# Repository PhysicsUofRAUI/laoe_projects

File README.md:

# laoe_projects
A place to hold all projects I have made while reading the book Learning The Art of Electronics

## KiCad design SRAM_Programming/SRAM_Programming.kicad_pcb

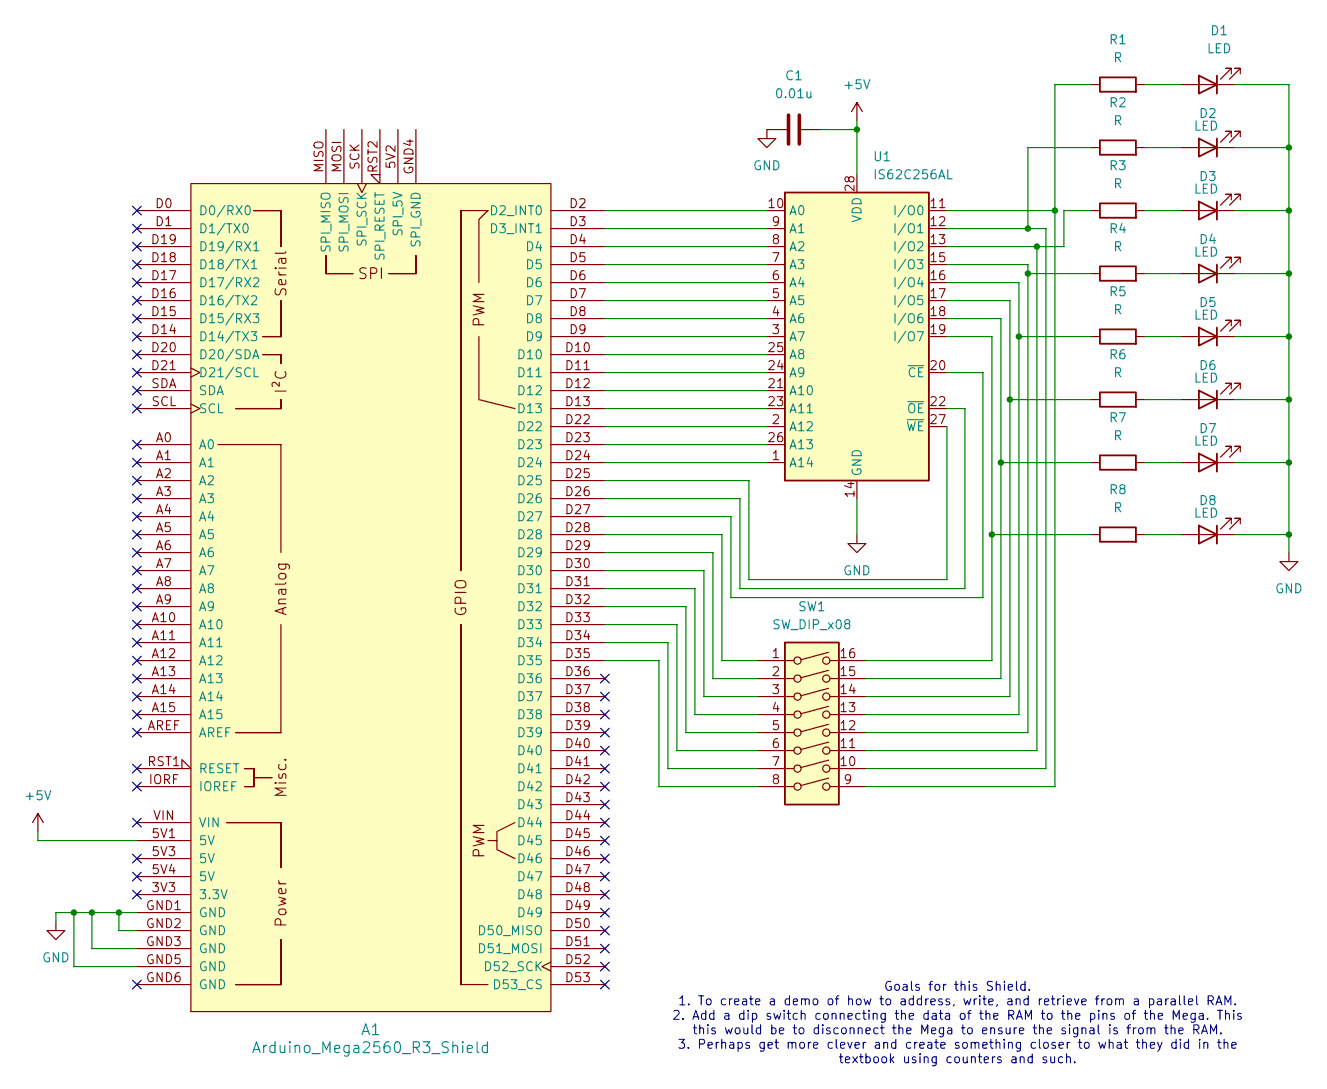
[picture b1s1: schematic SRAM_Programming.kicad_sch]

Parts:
A1: Arduino_Mega2560_R3_Shield
C1: 0.01u; C_0805_2012Metric_Pad1.18x1.45mm_HandSolder; MfG # C0805C103K5RACTU
D1, D2, D3, D4, D5, D6, D7, D8: LED; LED_D5.0mm; MfG # HLMP-D150
R1, R2, R3, R4, R5, R6, R7, R8: R; R_Axial_DIN0309_L9.0mm_D3.2mm_P12.70mm_Horizontal; MfG # CF14JT3K30
SW1: SW_DIP_x08; SW_DIP_SPSTx08_Slide_6.7x21.88mm_W7.62mm_P2.54mm_LowProfile; MfG # 208-8
U1: IS62C256AL; SOP-28_8.4x18.16mm_P1.27mm

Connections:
+5V: A1.5V1 (5V), C1.1, U1.28 (VDD)
GND: A1.GND1 (GND), A1.GND2 (GND), A1.GND3 (GND), A1.GND5 (GND), C1.2, D1.1 (K), D2.1 (K), D3.1 (K), D4.1 (K), D5.1 (K), D6.1 (K), D7.1 (K), D8.1 (K), U1.14 (GND)
unnamed: A1.D2 (D2_INT0), U1.10 (A0)
unnamed: A1.D3 (D3_INT1), U1.9 (A1)
unnamed: A1.D28, SW1.1
unnamed: A1.D29, SW1.2
unnamed: A1.D30, SW1.3
unnamed: A1.D31, SW1.4
unnamed: A1.D32, SW1.5
unnamed: A1.D33, SW1.6
unnamed: A1.D34, SW1.7
unnamed: A1.D35, SW1.8
unnamed: D1.2 (A), R1.2
unnamed: D2.2 (A), R2.2
unnamed: D3.2 (A), R3.2
unnamed: D4.2 (A), R4.2
unnamed: D5.2 (A), R5.2
unnamed: D6.2 (A), R6.2
unnamed: D7.2 (A), R7.2
unnamed: D8.2 (A), R8.2
unnamed: A1.D4, U1.8 (A2)
unnamed: A1.D5, U1.7 (A3)
unnamed: A1.D6, U1.6 (A4)
unnamed: A1.D7, U1.5 (A5)
unnamed: A1.D8, U1.4 (A6)
unnamed: A1.D9, U1.3 (A7)
unnamed: A1.D10, U1.25 (A8)
unnamed: A1.D11, U1.24 (A9)
unnamed: A1.D12, U1.21 (A10)
unnamed: A1.D13, U1.23 (A11)
unnamed: A1.D22, U1.2 (A12)
unnamed: A1.D23, U1.26 (A13)
unnamed: A1.D24, U1.1 (A14)
unnamed: R1.1, SW1.9, U1.11 (I/O0)
unnamed: R2.1, SW1.10, U1.12 (I/O1)
unnamed: R3.1, SW1.11, U1.13 (I/O2)
unnamed: R4.1, SW1.12, U1.15 (I/O3)
unnamed: R5.1, SW1.13, U1.16 (I/O4)
unnamed: R6.1, SW1.14, U1.17 (I/O5)
unnamed: R7.1, SW1.15, U1.18 (I/O6)
unnamed: R8.1, SW1.16, U1.19 (I/O7)
unnamed: A1.D27, U1.20 (~CE)
unnamed: A1.D26, U1.22 (~OE)
unnamed: A1.D25, U1.27 (~WE)

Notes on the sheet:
Goals for this Shield. 1. To create a demo of how to address, write, and retrieve from a parallel RAM. 2. Add a dip switch connecting the data of the RAM to the pins of the Mega. This this would be to disconnect the Mega to ensure the signal is from the RAM. 3. Perhaps get more clever and create so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

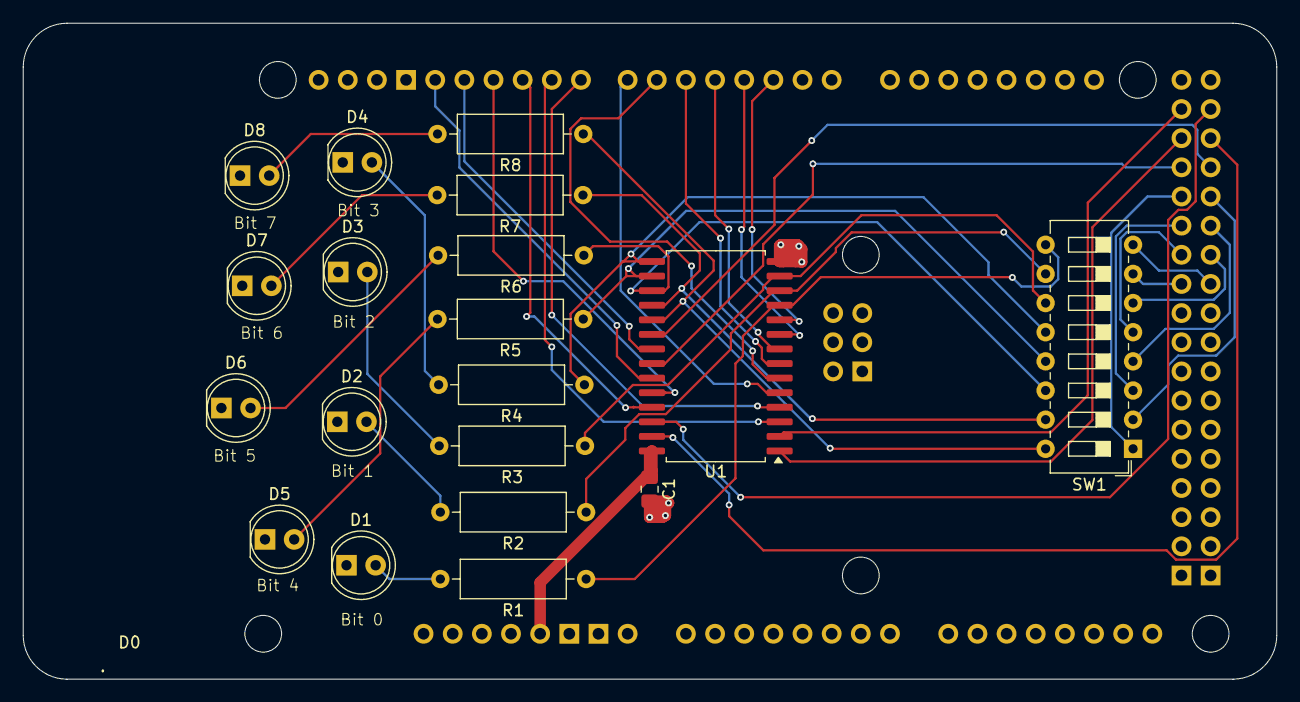
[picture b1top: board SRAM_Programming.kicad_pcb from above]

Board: 2 copper layers, 109.2 x 57.1 mm, 20 parts (0 on the bottom side), 44 nets.

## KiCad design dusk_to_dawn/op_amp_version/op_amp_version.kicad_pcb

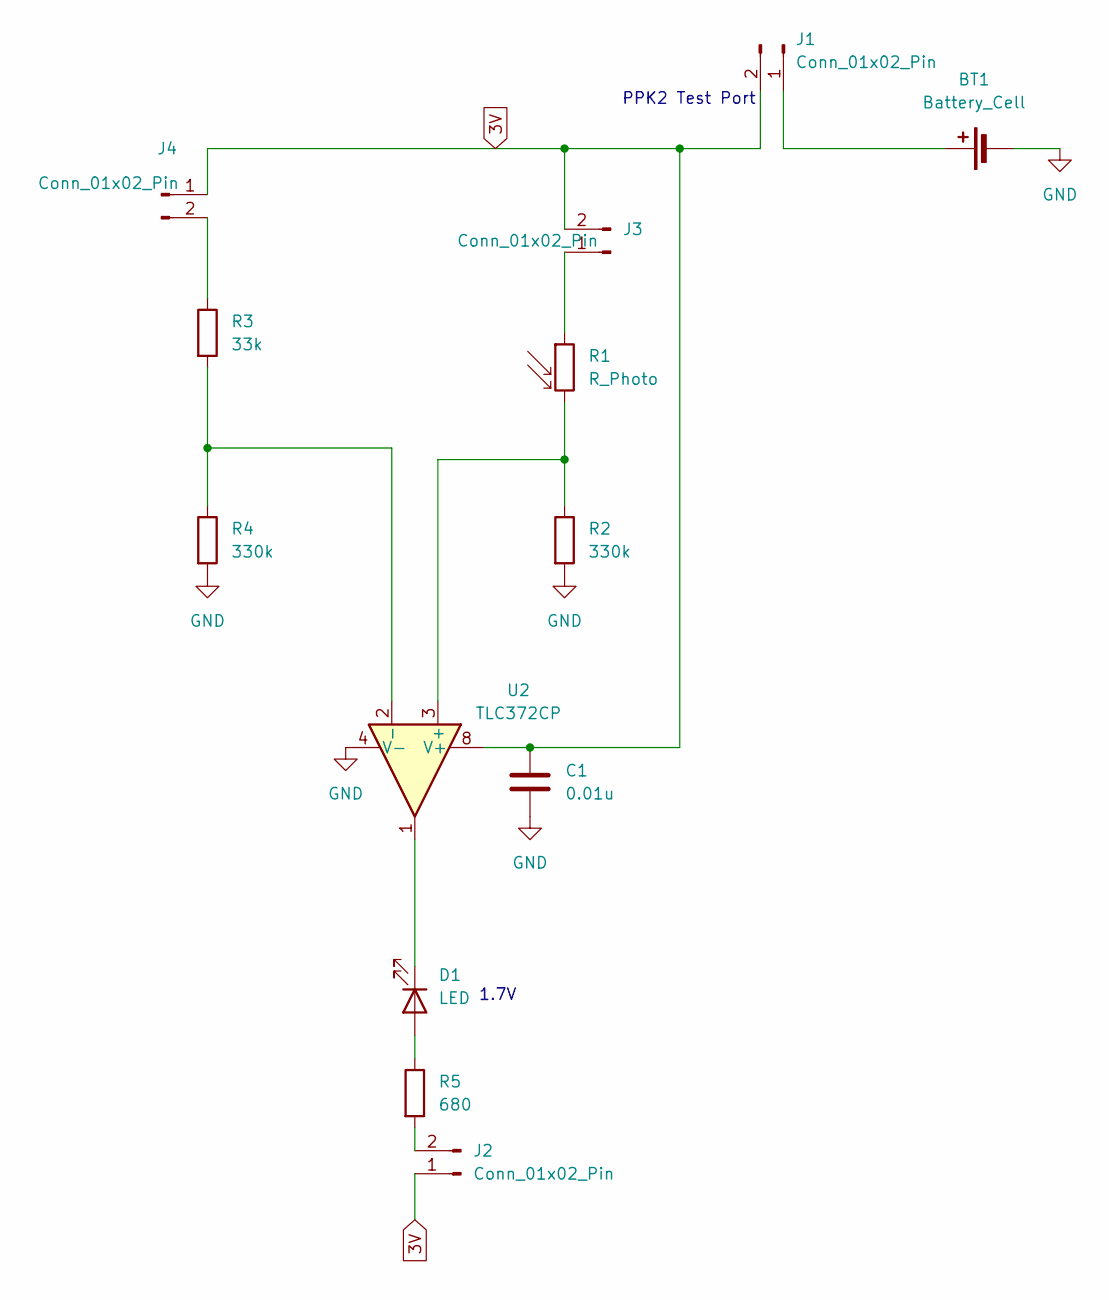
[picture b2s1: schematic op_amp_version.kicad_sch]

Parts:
BT1: Battery_Cell; SolderWire-0.1sqmm_1x02_P3.6mm_D0.4mm_OD1mm; MFG # 1066
C1: 0.01u; C_0805_2012Metric_Pad1.18x1.45mm_HandSolder; MfG # C0805C103K5RACTU
D1: LED; LED_D5.0mm; MFG # HLMP-D150
J1, J2, J3, J4: Conn_01x02_Pin; PinHeader_1x02_P2.54mm_Vertical; MFG # M20-9990246
R1: R_Photo; R_Axial_DIN0207_L6.3mm_D2.5mm_P7.62mm_Horizontal; MFG # PDV-P8104
R2: 330k; R_Axial_DIN0207_L6.3mm_D2.5mm_P7.62mm_Horizontal; MFG # CFM12JT33K0
R3: 33k; R_Axial_DIN0207_L6.3mm_D2.5mm_P7.62mm_Horizontal; MFG # CF12JT22K0
R4: 330k; R_Axial_DIN0207_L6.3mm_D2.5mm_P7.62mm_Horizontal; MFG # CF12JT22K0
R5: 680; R_Axial_DIN0207_L6.3mm_D2.5mm_P7.62mm_Horizontal; MFG # CF14JT680R
U2: TLC372CP; DIP-8_W7.62mm

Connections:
3V: C1.1, J1.2, J2.1, J3.2, J4.1, U2.8 (V+)
GND: BT1.2 (-), C1.2, R2.2, R4.2, U2.4 (V-)
unnamed: BT1.1 (+), J1.1
unnamed: D1.2 (A), R5.1
unnamed: D1.1 (K), U2.1
unnamed: J2.2, R5.2
unnamed: J3.1, R1.1
unnamed: J4.2, R3.1
unnamed: R1.2, R2.1, U2.3 (+)
unnamed: R3.2, R4.1, U2.2 (-)

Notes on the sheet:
1.7V
PPK2 Test Port

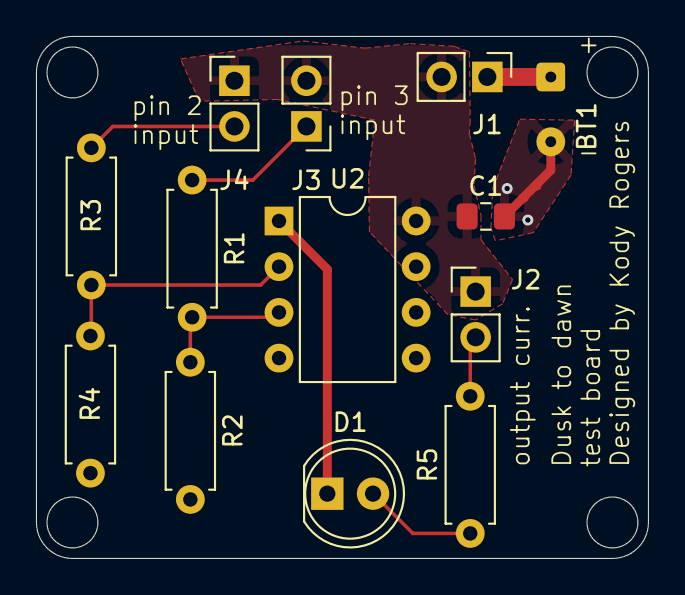
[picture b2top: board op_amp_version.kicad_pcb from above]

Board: 2 copper layers, 34.0 x 29.0 mm, 13 parts (0 on the bottom side), 10 nets.

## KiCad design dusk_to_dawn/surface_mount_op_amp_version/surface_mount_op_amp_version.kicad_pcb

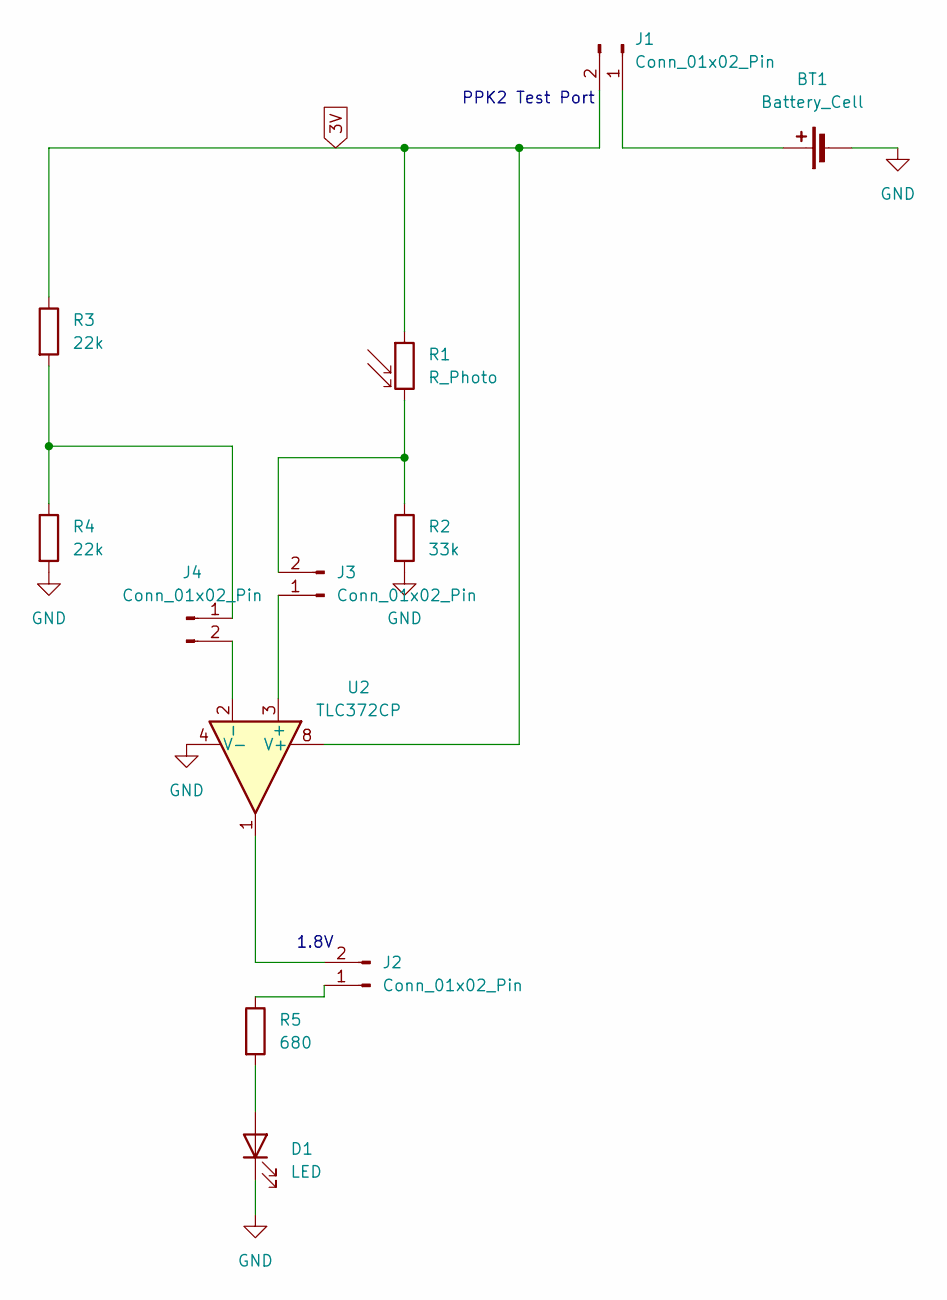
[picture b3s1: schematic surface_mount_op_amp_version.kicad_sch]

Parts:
BT1: Battery_Cell; Battery_Panasonic_CR2032-HFN_Horizontal_CircularHoles; MFG # 1066
D1: LED; LED_D5.0mm; MFG # HLMP-D150
J1, J2, J3, J4: Conn_01x02_Pin; PinHeader_1x02_P2.54mm_Vertical; MFG # M20-9990246
R1: R_Photo; R_Axial_DIN0207_L6.3mm_D2.5mm_P7.62mm_Horizontal; MFG # PDV-P8104
R2: 33k; R_Axial_DIN0207_L6.3mm_D2.5mm_P7.62mm_Horizontal; MFG # CFM12JT33K0
R3, R4: 22k; R_Axial_DIN0207_L6.3mm_D2.5mm_P7.62mm_Horizontal; MFG # CF12JT22K0
R5: 680; R_Axial_DIN0207_L6.3mm_D2.5mm_P7.62mm_Horizontal; MFG # CF14JT680R
U2: TLC372CP; SOIC-8_3.9x4.9mm_P1.27mm

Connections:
3V: J1.2, R1.1, R3.1, U2.8 (V+)
GND: BT1.2 (-), D1.1 (K), R2.2, R4.2, U2.4 (V-)
unnamed: BT1.1 (+), J1.1
unnamed: D1.2 (A), R5.2
unnamed: J2.1, R5.1
unnamed: J2.2, U2.1
unnamed: J3.1, U2.3 (+)
unnamed: J3.2, R1.2, R2.1
unnamed: J4.1, R3.2, R4.1
unnamed: J4.2, U2.2 (-)

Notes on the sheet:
1.8V
PPK2 Test Port

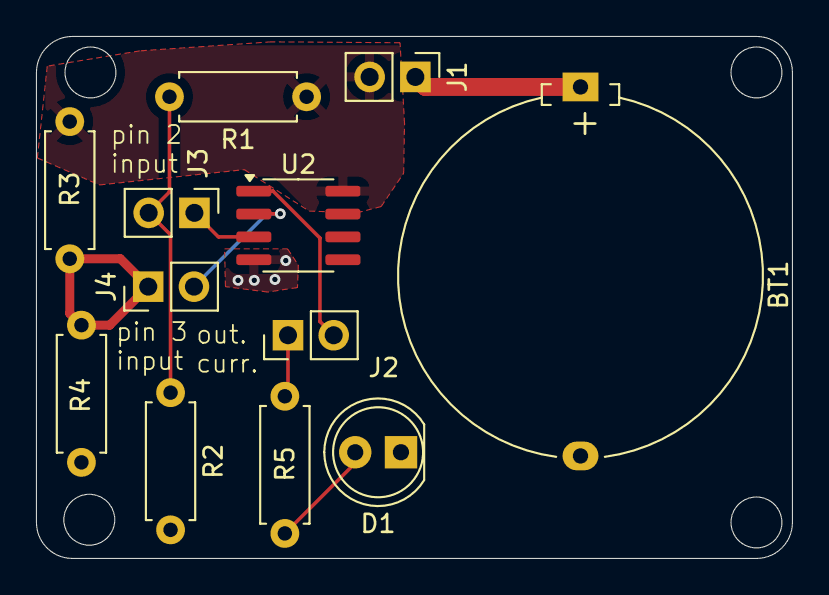
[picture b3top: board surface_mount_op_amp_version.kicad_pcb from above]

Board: 2 copper layers, 42.0 x 29.0 mm, 12 parts (0 on the bottom side), 10 nets.

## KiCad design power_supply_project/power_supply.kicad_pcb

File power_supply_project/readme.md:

# Intro
This project is part of my learning for the learning the Art of Electronics. It is a simple power supply that I made based on what I've learned.

# Regulator calculations
## Output Voltage
Vref = 1.25V

R2 = 2k

R4 = 2.2k

R5 = 0 - 10k

Next part is going to ignore the I<sub>ref</sub> error term that comes out of the reference terminal for simplicity.

Vout ~ Vref[1 + (R4+R5)/R2]

The minimum Vout would then be:
Vout = 1.25V + 1.25V(2.2k/2k)
     = 2.6V

The maximum Vout would then be:
Vout = 1.25V + 1.25V(12.2k/2k)
     = 8.9V

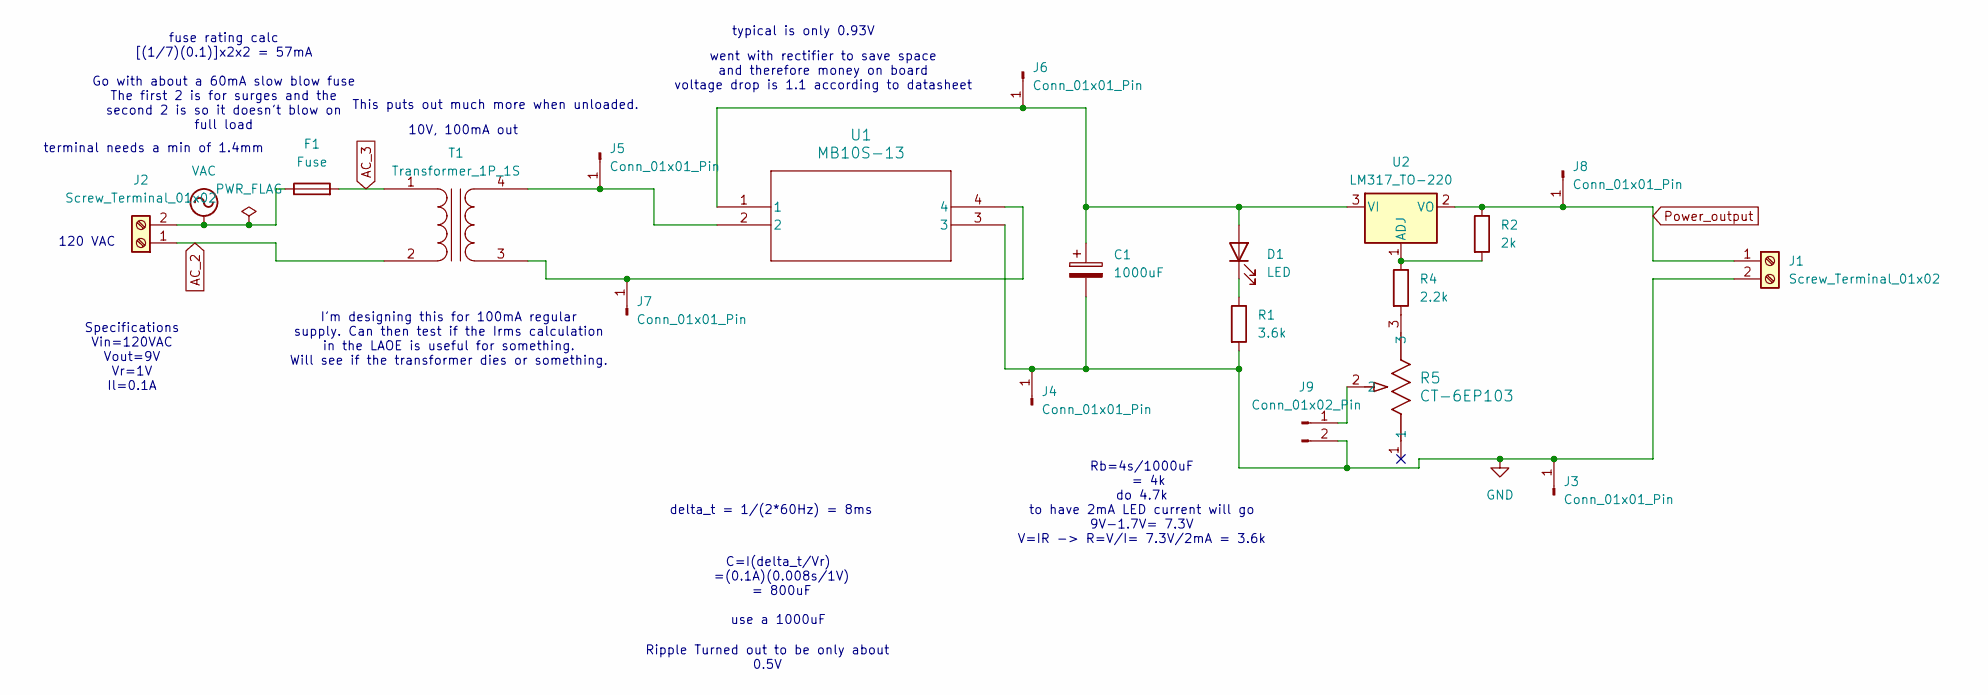
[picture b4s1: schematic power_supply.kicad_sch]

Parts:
C1: 1000uF; CP_Radial_D10.0mm_P5.00mm; Part # 25PX1000MEFCT810X16
D1: LED; LED_D5.0mm; Part # Red 626nm LED Indication - Discrete 1.7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
F1: Fuse; Fuseholder_Clip-5x20mm_Bel_FC-203-22_Lateral_P17.80x5.00mm_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
J1: Screw_Terminal_01x02; TerminalBlock_4Ucon_1x02_P3.50mm_Vertical; Part # OSTTE020104
J2: Screw_Terminal_01x02; Altech_AK100_1x02_P5.00mm; Part # 691137710002
J3, J4, J5, J6, J7, J8: Conn_01x01_Pin; PinHeader_1x01_P2.54mm_Vertical; Part # TS-103-T-A
J9: Conn_01x02_Pin; PinHeader_1x02_P2.54mm_Vertical; MFG # M20-9990246
R1: 3.6k; R_Axial_DIN0207_L6.3mm_D2.5mm_P7.62mm_Horizontal; Part # CF12JT3K60
R2: 2k; R_Axial_DIN0207_L6.3mm_D2.5mm_P7.62mm_Horizontal; Mfg # RNF14FTD2K00
R4: 2.2k; R_Axial_DIN0207_L6.3mm_D2.5mm_P7.62mm_Horizontal; Mfg # CF14JT2K20
R5: CT-6EP103; POT_CT-6EP103_NDC; Mfg # CT-6EP103
T1: Transformer_1P_1S; BV301S10010 Transformer; Part # BV301S10010
U1: MB10S-13; TO-269AA_3P8X4P75_DIO-L; Part # MB10S-13
U2: LM317_TO-220; TO-220-3_Vertical; MfG # LM317HVT/NOPB

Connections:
AC_2: J2.1, T1.2 (AB)
AC_3: F1.2, T1.1 (AA)
GND: C1.2, J1.2, J3.1, J4.1, J9.2, R1.2, U1.3
unnamed: C1.1, D1.2 (A), J6.1, U1.1, U2.3 (VI)
unnamed: D1.1 (K), R1.1
unnamed: J5.1, T1.4 (SB), U1.2
unnamed: J7.1, T1.3 (SA), U1.4
unnamed: J9.1, R5.2
unnamed: R4.2, R5.3
unnamed: R2.2, R4.1, U2.1 (ADJ)
Power_output: J1.1, J8.1, R2.1, U2.2 (VO)
VAC: F1.1, J2.2

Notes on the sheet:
Ripple Turned out to be only about 0.5V
Rb=4s/1000uF = 4k do 4.7k to have 2mA LED current will go 9V-1.7V= 7.3V V=IR -> R=V/I= 7.3V/2mA = 3.6k
fuse rating calc [(1/7)(0.1)]x2x2 = 57mA Go with about a 60mA slow blow fuse The first 2 is for surges and the second 2 is so it doesn't blow on full load
terminal needs a min of 1.4mm
delta_t = 1/(2*60Hz) = 8ms
10V, 100mA out
typical is only 0.93V
I'm designing this for 100mA regular supply. Can then test if the Irms calculation in the LAOE is useful for something. Will see if the transformer dies or something.
Specifications Vin=120VAC Vout=9V Vr=1V Il=0.1A
120 VAC
This puts out much more when unloaded.
C=I(delta_t/Vr) =(0.1A)(0.008s/1V) = 800uF use a 1000uF
went with rectifier to save space and therefore money on board voltage drop is 1.1 according to datasheet

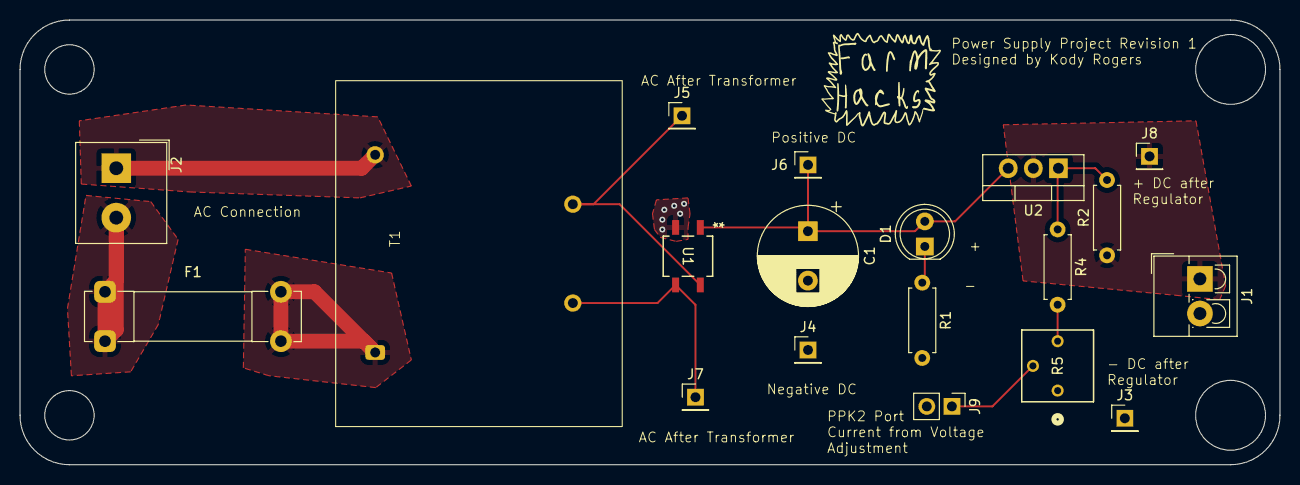
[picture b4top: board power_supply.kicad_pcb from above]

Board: 2 copper layers, 127.5 x 45.0 mm, 19 parts (0 on the bottom side), 12 nets.

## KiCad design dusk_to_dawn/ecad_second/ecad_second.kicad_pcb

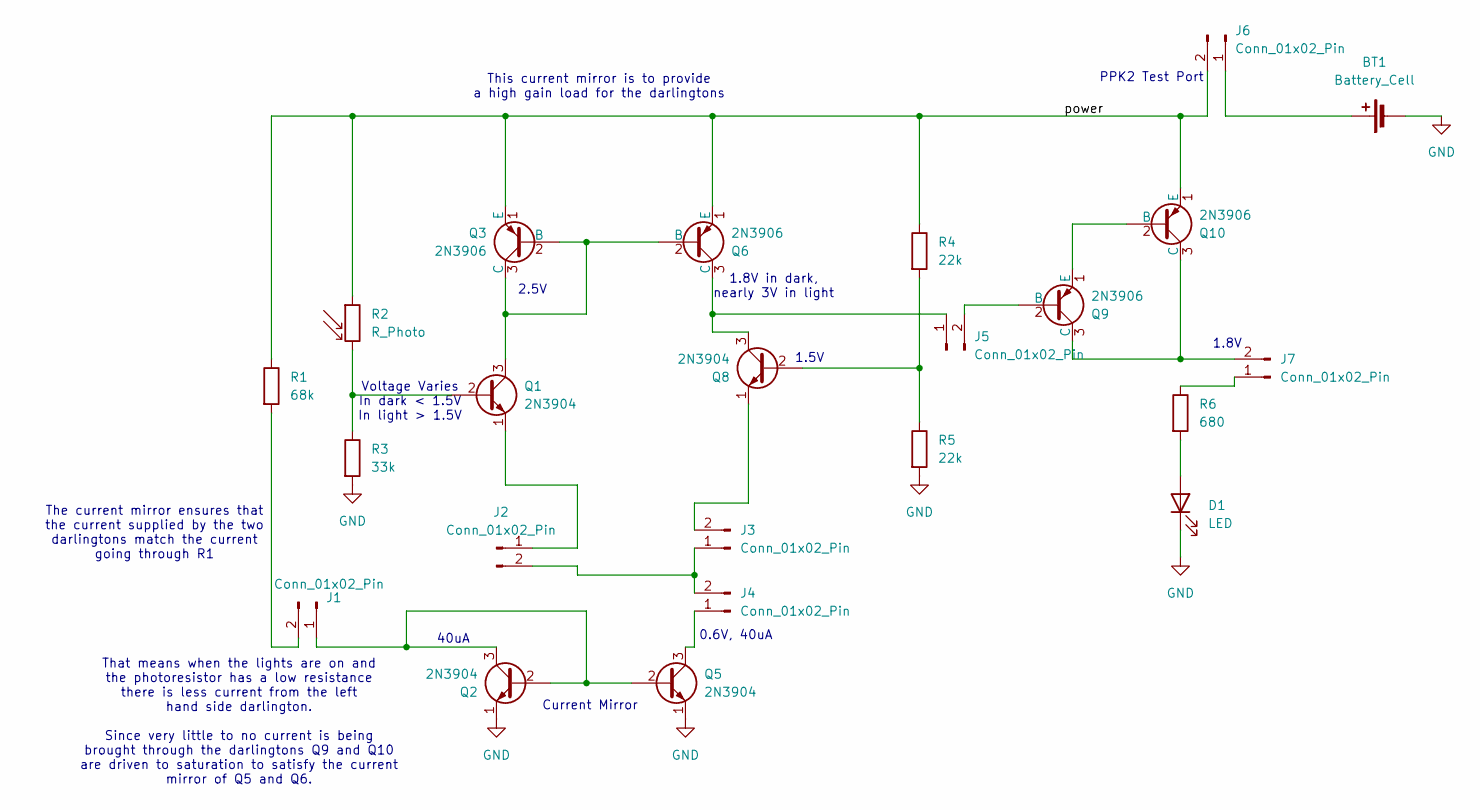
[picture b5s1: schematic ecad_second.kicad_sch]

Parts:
BT1: Battery_Cell; Battery_Panasonic_CR2032-HFN_Horizontal_CircularHoles; MFG # 1066
D1: LED; LED_D5.0mm; MFG # HLMP-D150
J1, J2, J3, J4, J5, J6, J7: Conn_01x02_Pin; PinHeader_1x02_P2.54mm_Vertical; MFG # M20-9990246
Q1, Q2, Q5, Q8: 2N3904; TO-92_Inline_Wide; MFG # 2N3904
Q3, Q6, Q9, Q10: 2N3906; TO-92_Inline_Wide; MFG # 2N3906
R1: 68k; R_Axial_DIN0207_L6.3mm_D2.5mm_P7.62mm_Horizontal; MFG # MFR50SFTE52-68K
R2: R_Photo; R_Axial_DIN0204_L3.6mm_D1.6mm_P5.08mm_Horizontal; MFG # PDV-P8104
R3: 33k; R_Axial_DIN0207_L6.3mm_D2.5mm_P7.62mm_Horizontal; MFG # CFM12JT33K0
R4, R5: 22k; R_Axial_DIN0207_L6.3mm_D2.5mm_P7.62mm_Horizontal; MFG # CF12JT22K0
R6: 680; R_Axial_DIN0207_L6.3mm_D2.5mm_P7.62mm_Horizontal; MFG # CF14JT680R

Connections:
/power: J6.2, Q3.1 (E), Q6.1 (E), Q10.1 (E), R1.1, R2.1, R4.1
GND: BT1.2 (-), D1.1 (K), Q2.1 (E), Q5.1 (E), R3.2, R5.2
unnamed: BT1.1 (+), J6.1
unnamed: D1.2 (A), R6.2
unnamed: J1.1, Q2.2 (B), Q2.3 (C), Q5.2 (B)
unnamed: J1.2, R1.2
unnamed: J2.1, Q1.1 (E)
unnamed: J2.2, J3.1, J4.2
unnamed: J3.2, Q8.1 (E)
unnamed: J4.1, Q5.3 (C)
unnamed: J5.1, Q6.3 (C), Q8.3 (C)
unnamed: J5.2, Q9.2 (B)
unnamed: J7.1, R6.1
unnamed: J7.2, Q9.3 (C), Q10.3 (C)
unnamed: Q1.2 (B), R2.2, R3.1
unnamed: Q1.3 (C), Q3.2 (B), Q3.3 (C), Q6.2 (B)
unnamed: Q8.2 (B), R4.2, R5.1
unnamed: Q9.1 (E), Q10.2 (B)

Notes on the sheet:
Voltage Varies In dark < 1.5V In light > 1.5V
That means when the lights are on and the photoresistor has a low resistance there is less current from the left hand side darlington. Since very little to no current is being brought through the darlingtons Q9 and Q10 are driven to saturation to satisfy the current mirror of Q5 and Q6.
1.8V
40uA
This current mirror is to provide a high gain load for the darlingtons
The current mirror ensures that the current supplied by the two darlingtons match the current going through R1
1.5V
2.5V
0.6V, 40uA
PPK2 Test Port
1.8V in dark, nearly 3V in light
Current Mirror

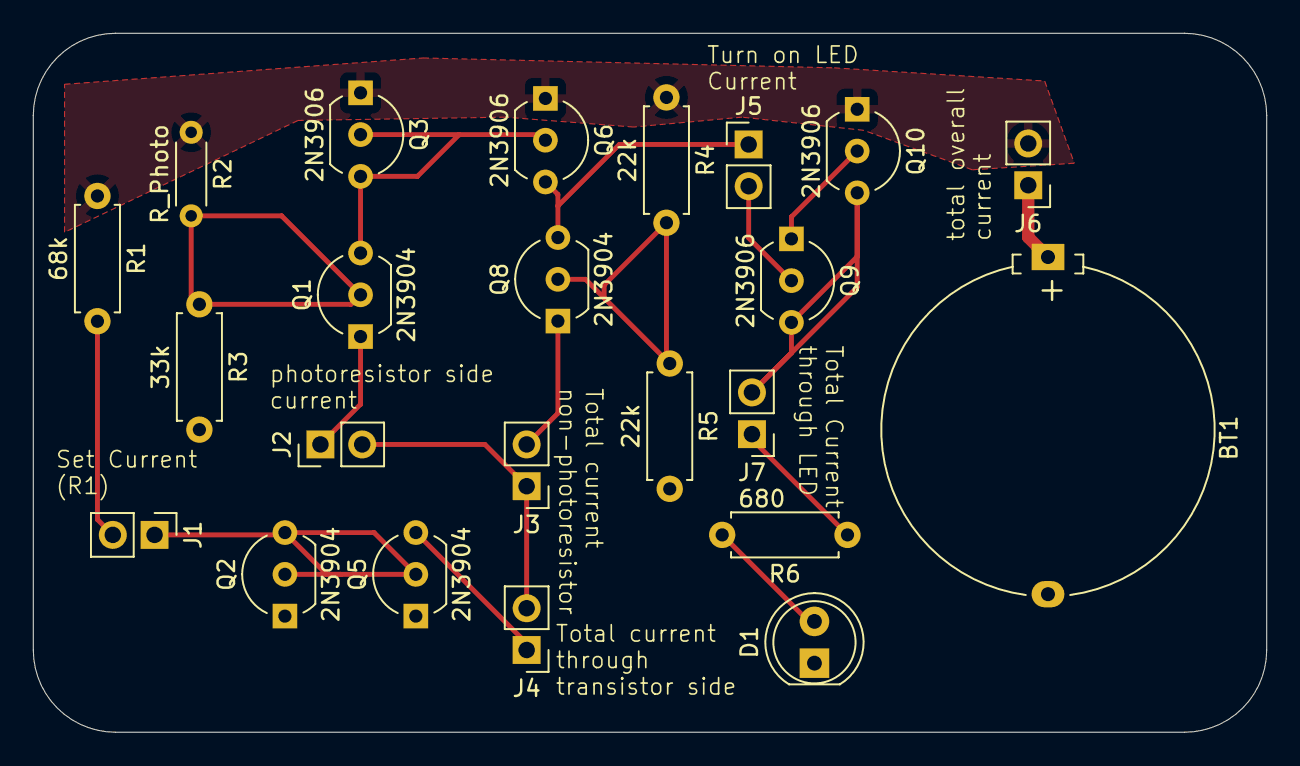
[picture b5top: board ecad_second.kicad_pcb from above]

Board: 2 copper layers, 75.0 x 42.5 mm, 23 parts (0 on the bottom side), 18 nets.

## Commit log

2024-12-18 update gitignore to ignore my gerber files
2024-12-18 add first draft of the part two project
2024-12-22 add some analysis
2025-01-02 update gitignore to ignore gerbers
2025-01-02 update gitignore to ignore gerbers another folder
2025-01-02 add first version of power supply
2025-01-02 add linear regulator and trimmer resistor to schematic
2025-01-02 fix ERC errors and add footprint for ppk2 test point
2025-01-03 Add a few net labels
2025-01-03 update pcb layout to include linear regulator
2025-01-03 update pcb and schematic images
2025-01-19 update gitignore
2025-01-19 added notes and such
2025-01-19 created a readme for the the powersupply project. May become a report later
2025-01-26 updated the power supply readme
2025-01-26 add kicad files of first draft of op amp dusk to dawn
2025-02-08 add first version of op amp dusk to dawn
2025-02-08 add sram demo/learning board
2025-02-08 started pcb layout
2025-02-09 Finish first version of sram shield
2025-03-14 Add short tutorial on diode clamps
